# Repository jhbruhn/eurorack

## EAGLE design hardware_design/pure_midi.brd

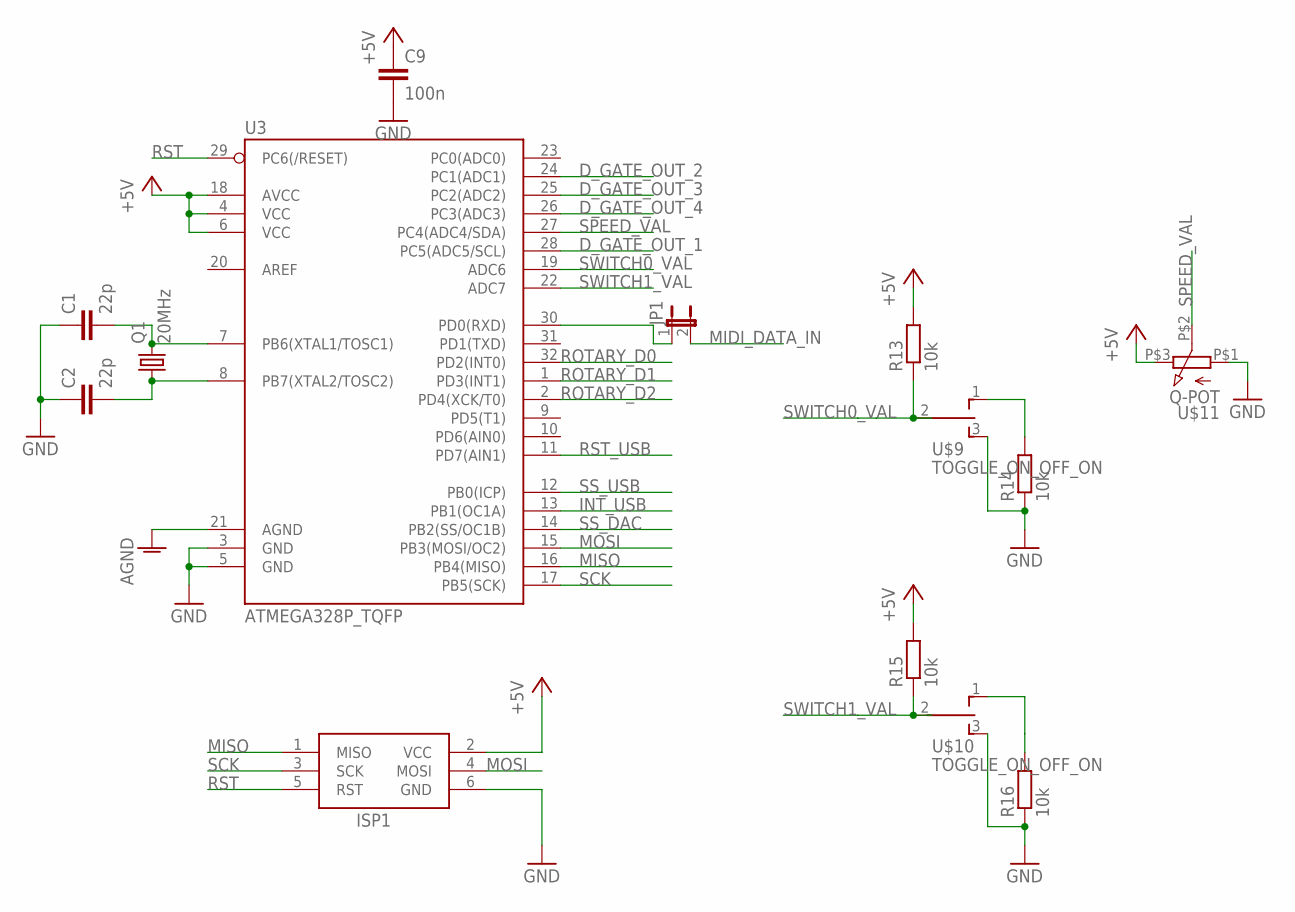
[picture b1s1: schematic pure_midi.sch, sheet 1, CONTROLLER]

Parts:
C1, C2: 22p; C0805
C9: 100n; C0805
ISP1: AVRISP-6; AVRISP
JP1: JP1E; JP1
Q1: 20MHz; HC49UP
R13, R14, R15, R16: 10k; R0805
U3: ATMEGA328P_TQFP; TQFP32-08
U$9, U$10: TOGGLE_ON_OFF_ON
U$11: Q-POT

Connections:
+5V: C9.1, ISP1.2 (VCC), R13.2, R15.2, U3.4 (VCC), U3.6 (VCC), U3.18 (AVCC), U$11.P$3 (3); also elsewhere on the board
D_GATE_OUT_1: U3.28 (PC5(ADC5/SCL)); also elsewhere on the board
D_GATE_OUT_2: U3.24 (PC1(ADC1)); also elsewhere on the board
D_GATE_OUT_3: U3.25 (PC2(ADC2)); also elsewhere on the board
D_GATE_OUT_4: U3.26 (PC3(ADC3)); also elsewhere on the board
GND: C1.1, C2.1, C9.2, ISP1.6 (GND), R14.1, R16.1, U3.3 (GND), U3.5 (GND), U3.21 (AGND), U$9.3 (S), U$10.3 (S), U$11.P$1 (1); also elsewhere on the board
INT_USB: U3.13 (PB1(OC1A)); also elsewhere on the board
MIDI_DATA_IN: JP1.2; also elsewhere on the board
MISO: ISP1.1 (MISO), U3.16 (PB4(MISO)); also elsewhere on the board
MOSI: ISP1.4 (MOSI), U3.15 (PB3(MOSI/OC2)); also elsewhere on the board
unnamed: C1.2, Q1.2, U3.7 (PB6(XTAL1/TOSC1))
unnamed: C2.2, Q1.1, U3.8 (PB7(XTAL2/TOSC2))
unnamed: JP1.1, U3.30 (PD0(RXD))
unnamed: R16.2, U$10.1 (O)
unnamed: R14.2, U$9.1 (O)
ROTARY_D0: U3.32 (PD2(INT0)); also elsewhere on the board
ROTARY_D1: U3.1 (PD3(INT1)); also elsewhere on the board
ROTARY_D2: U3.2 (PD4(XCK/T0)); also elsewhere on the board
RST: ISP1.5 (RST), U3.29 (PC6(/RESET))
RST_USB: U3.11 (PD7(AIN1)); also elsewhere on the board
SCK: ISP1.3 (SCK), U3.17 (PB5(SCK)); also elsewhere on the board
SPEED_VAL: U3.27 (PC4(ADC4/SDA)), U$11.P$2 (2)
SS_DAC: U3.14 (PB2(SS/OC1B)); also elsewhere on the board
SS_USB: U3.12 (PB0(ICP)); also elsewhere on the board
SWITCH0_VAL: R13.1, U3.19 (ADC6), U$9.2
SWITCH1_VAL: R15.1, U3.22 (ADC7), U$10.2

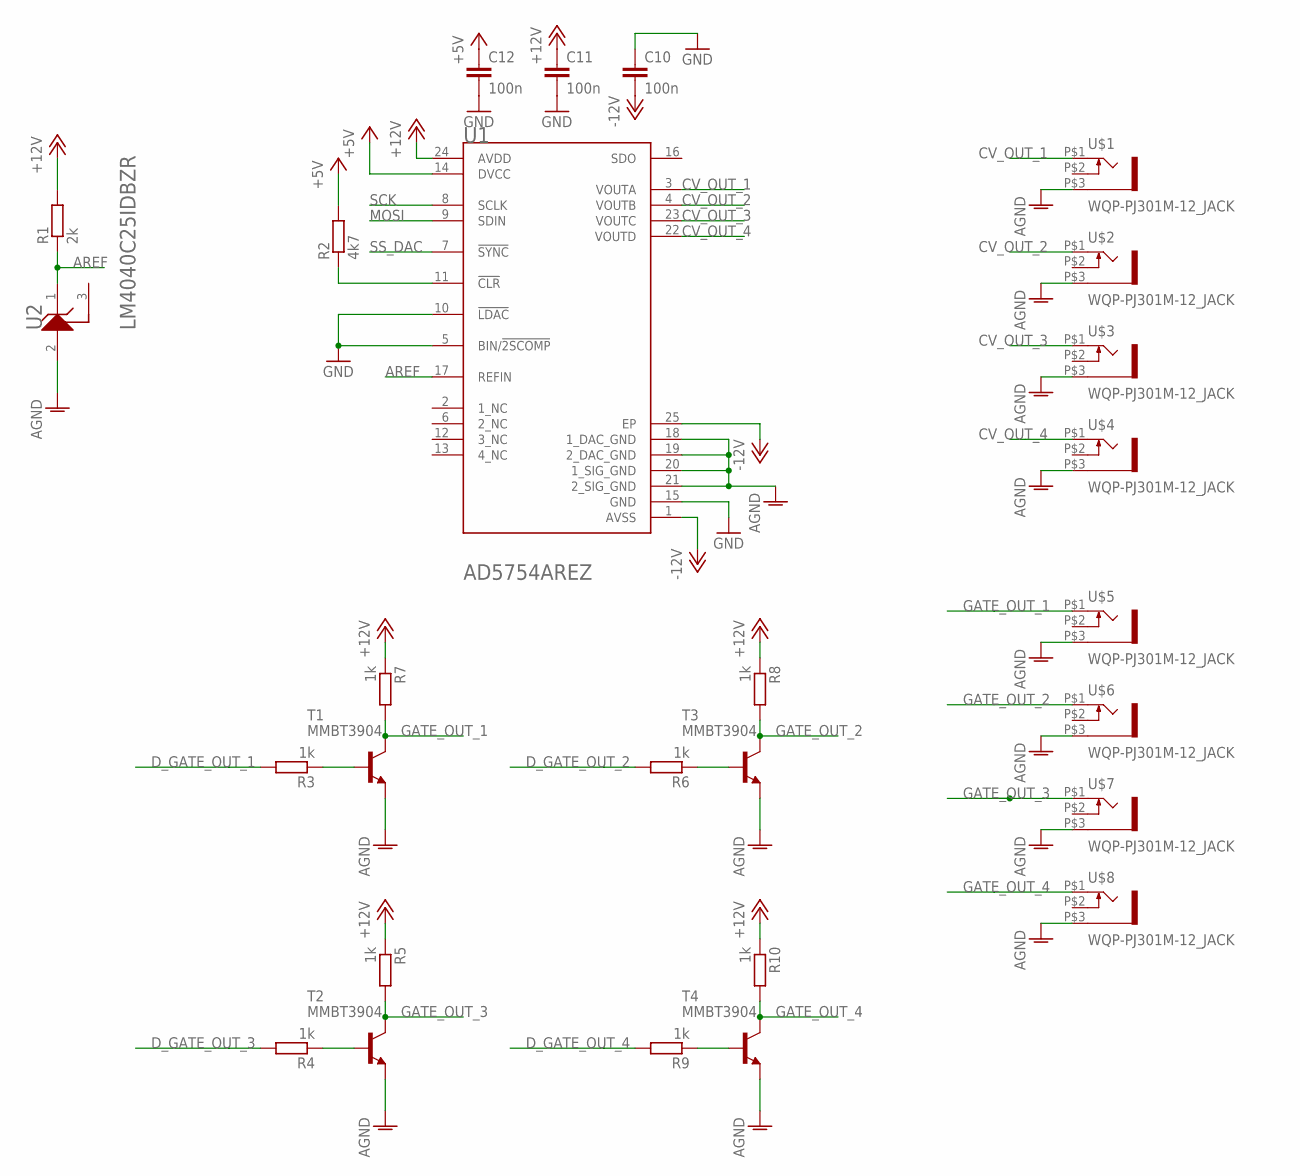
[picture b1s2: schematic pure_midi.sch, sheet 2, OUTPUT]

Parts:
C10, C11, C12: 100n; C0805
R1: 2k; R0805
R2: 4k7; R0805
R3, R4, R5, R6, R7, R8, R9, R10: 1k; R0805
T1, T2, T3, T4: MMBT3904; SOT23-EBC
U1: ANALOG_DEVICES_INC_AD5754AREZANALOG_DEVICES_INC_A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; ANALOG_DEVICES_INC_AD5754AREZ_0
U2: TEXAS_INSTRUMENTS_LM4040C25IDBZRTEXAS_INSTRUMENTS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; TEXAS_INSTRUMENTS_LM4040C25IDBZR_1
U$1, U$2, U$3, U$4, U$5, U$6, U$7, U$8: WQP-PJ301M-12_JACK

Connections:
+5V: C12.1, R2.2, U1.14 (DVCC); also elsewhere on the board
+12V: C11.1, R1.2, R5.1, R7.1, R8.1, R10.1, U1.24 (AVDD); also elsewhere on the board
-12V: C10.2, U1.1 (AVSS), U1.25 (EP); also elsewhere on the board
AREF: R1.1, U1.17 (REFIN), U2.1 (CATHODE)
CV_OUT_1: U1.3 (VOUTA), U$1.P$1 (2)
CV_OUT_2: U1.4 (VOUTB), U$2.P$1 (2)
CV_OUT_3: U1.23 (VOUTC), U$3.P$1 (2)
CV_OUT_4: U1.22 (VOUTD), U$4.P$1 (2)
D_GATE_OUT_1: R3.2; also elsewhere on the board
D_GATE_OUT_2: R6.2; also elsewhere on the board
D_GATE_OUT_3: R4.2; also elsewhere on the board
D_GATE_OUT_4: R9.2; also elsewhere on the board
GATE_OUT_1: R7.2, T1.C, U$5.P$1 (2)
GATE_OUT_2: R8.2, T3.C, U$6.P$1 (2)
GATE_OUT_3: R5.2, T2.C, U$7.P$1 (2)
GATE_OUT_4: R10.2, T4.C, U$8.P$1 (2)
GND: C10.1, C11.2, C12.2, T1.E, T2.E, T3.E, T4.E, U1.5 (BIN/!2SCOMP!), U1.10 (!LDAC!), U1.15 (GND), U1.18 (1_DAC_GND), U1.19 (2_DAC_GND), U1.20 (1_SIG_GND), U1.21 (2_SIG_GND), U2.2 (ANODE), U$1.P$3 (1), U$2.P$3 (1), U$3.P$3 (1), U$4.P$3 (1), U$5.P$3 (1), U$6.P$3 (1), U$7.P$3 (1), U$8.P$3 (1); also elsewhere on the board
MOSI: U1.9 (SDIN); also elsewhere on the board
unnamed: R2.1, U1.11 (!CLR!)
unnamed: R3.1, T1.B
unnamed: R4.1, T2.B
unnamed: R6.1, T3.B
unnamed: R9.1, T4.B
SCK: U1.8 (SCLK); also elsewhere on the board
SS_DAC: U1.7 (!SYNC!); also elsewhere on the board

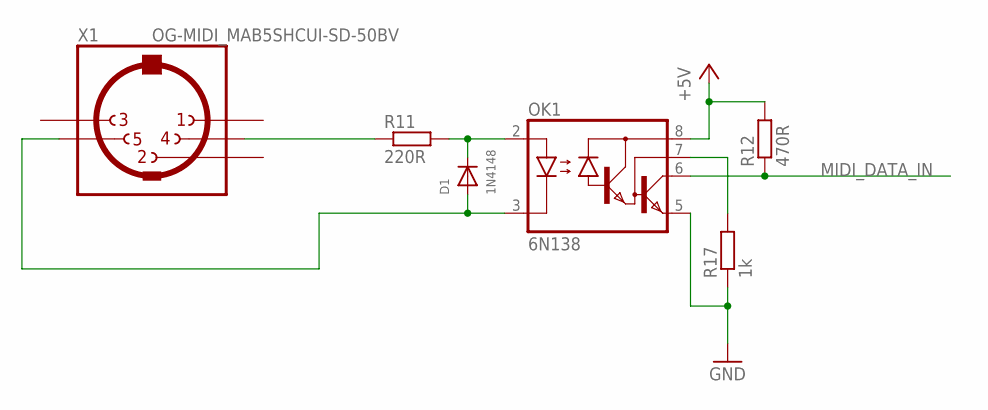
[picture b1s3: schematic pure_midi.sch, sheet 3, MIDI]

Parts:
D1: 1N4148; SOD-323F
OK1: 6N138; DIL08
R11: 220R; R0805
R12: 470R; R0805
R17: 1k; R0805
X1: OG-MIDI_MAB5SHCUI-SD-50BV; OG-MIDI_SD-50BV

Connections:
+5V: OK1.8 (VCC), R12.2; also elsewhere on the board
GND: OK1.5 (GND), R17.1; also elsewhere on the board
MIDI_DATA_IN: OK1.6 (VO), R12.1; also elsewhere on the board
unnamed: D1.C, OK1.2 (A), R11.2
unnamed: R11.1, X1.4
unnamed: D1.A, OK1.3 (C), X1.5
unnamed: OK1.7 (VB), R17.2

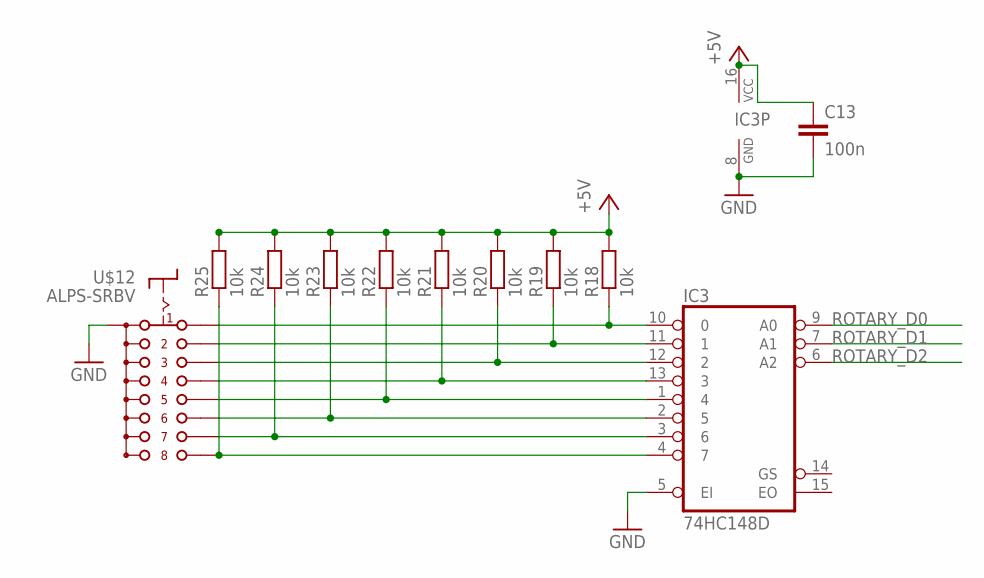
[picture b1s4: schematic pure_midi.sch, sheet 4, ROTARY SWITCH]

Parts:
C13: 100n; C0805
IC3: 74HC148D; SO16
R18, R19, R20, R21, R22, R23, R24, R25: 10k; R0805
U$12: ALPS-SRBV

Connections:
+5V: C13.1, IC3.16 (VCC), R18.2, R19.2, R20.2, R21.2, R22.2, R23.2, R24.2, R25.2; also elsewhere on the board
GND: C13.2, IC3.5 (EI), IC3.8 (GND), U$12.COM (A), U$12.COM2 (A); also elsewhere on the board
unnamed: IC3.10 (0), R18.1, U$12.A (1)
unnamed: IC3.11 (1), R19.1, U$12.B (2)
unnamed: IC3.12 (2), R20.1, U$12.C (3)
unnamed: IC3.13 (3), R21.1, U$12.D (4)
unnamed: IC3.1 (4), R22.1, U$12.E (5)
unnamed: IC3.2 (5), R23.1, U$12.F (6)
unnamed: IC3.3 (6), R24.1, U$12.G (7)
unnamed: IC3.4 (7), R25.1, U$12.H (8)
ROTARY_D0: IC3.9 (A0); also elsewhere on the board
ROTARY_D1: IC3.7 (A1); also elsewhere on the board
ROTARY_D2: IC3.6 (A2); also elsewhere on the board

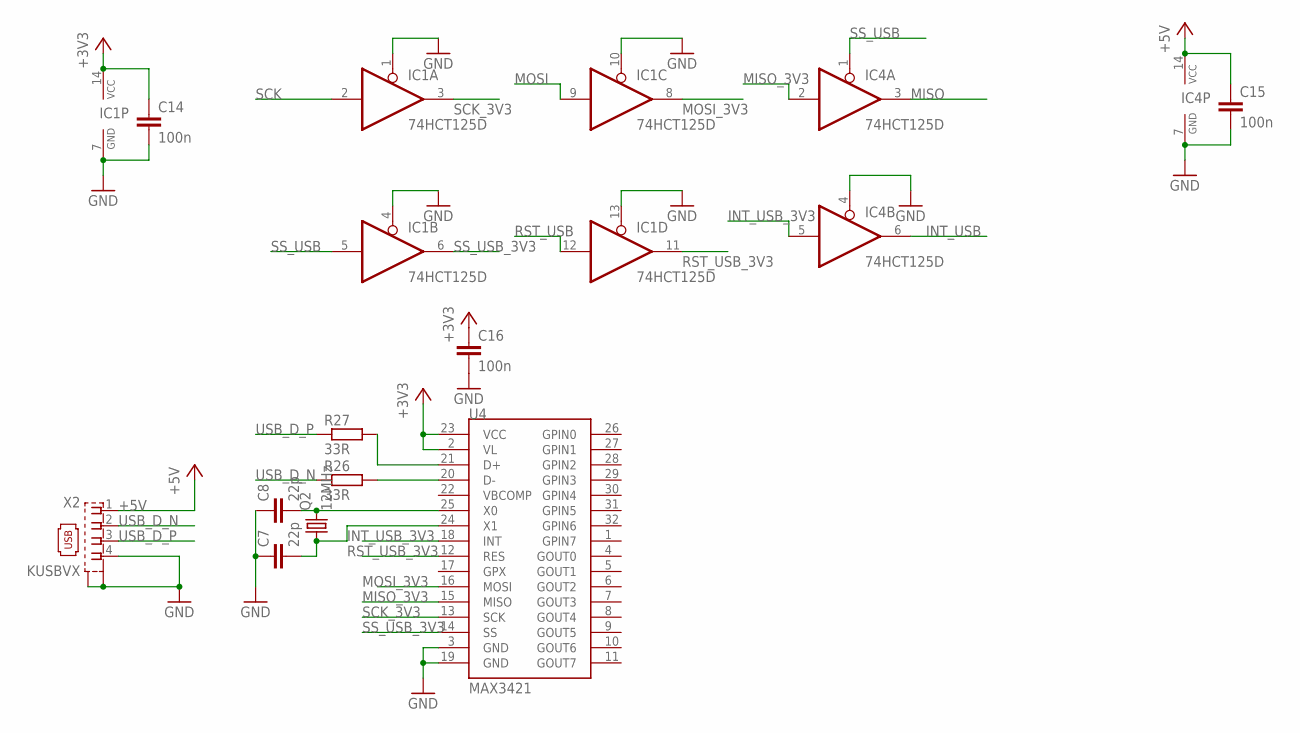
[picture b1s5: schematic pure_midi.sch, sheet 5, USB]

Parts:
C7, C8: 22p; C0805
C14, C15, C16: 100n; C0805
IC1, IC4: 74HCT125D; SO14
Q2: 12MHz; HC49UP
R26, R27: 33R; R0805
U4: MAX3421; TQFP32-5MM
X2: KUSBVX

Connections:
+3V3: C14.1, C16.1, IC1.14 (VCC), U4.2 (VL), U4.23 (VCC); also elsewhere on the board
+5V: C15.1, IC4.14 (VCC), X2.1; also elsewhere on the board
GND: C7.1, C8.1, C14.2, C15.2, C16.2, IC1.1 (OE), IC1.4 (OE), IC1.7 (GND), IC1.10 (OE), IC1.13 (OE), IC4.4 (OE), IC4.7 (GND), U4.3 (GND), U4.19 (GND), X2.4, X2.M1 (S1), X2.M2 (S2); also elsewhere on the board
INT_USB: IC4.6 (O); also elsewhere on the board
INT_USB_3V3: IC4.5 (I), U4.18 (INT)
MISO: IC4.3 (O); also elsewhere on the board
MISO_3V3: IC4.2 (I), U4.15 (MISO)
MOSI: IC1.9 (I); also elsewhere on the board
MOSI_3V3: IC1.8 (O), U4.16 (MOSI)
unnamed: C8.2, Q2.2, U4.25 (X0)
unnamed: C7.2, Q2.1, U4.24 (X1)
RST_USB: IC1.12 (I); also elsewhere on the board
RST_USB_3V3: IC1.11 (O), U4.12 (RES)
SCK: IC1.2 (I); also elsewhere on the board
SCK_3V3: IC1.3 (O), U4.13 (SCK)
SS_USB: IC1.5 (I), IC4.1 (OE); also elsewhere on the board
SS_USB_3V3: IC1.6 (O), U4.14 (SS)
USB_D_N: R26.1, X2.2
USB_D_P: R27.1, X2.3
USB_N: R26.2, U4.20 (D-)
USB_P: R27.2, U4.21 (D+)

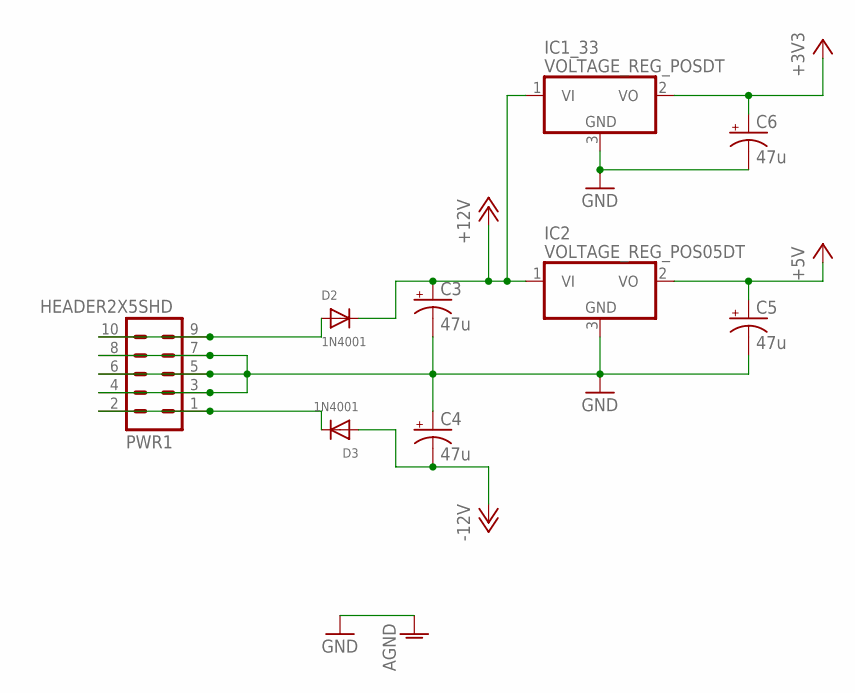
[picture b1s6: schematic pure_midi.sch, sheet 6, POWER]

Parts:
C3, C4, C5, C6: 47u; 153CLV-0505
D2, D3: 1N4001; SMADIODE
IC1_33: VOLTAGE_REG_POSDT; TO252
IC2: VOLTAGE_REG_POS05DT; TO252
PWR1: HEADER2X5SHD; 2X5-SHROUDED

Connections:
+3V3: C6.+, IC1_33.2 (VO); also elsewhere on the board
+5V: C5.+, IC2.2 (VO); also elsewhere on the board
+12V: C3.+, D2.C, IC1_33.1 (VI), IC2.1 (VI); also elsewhere on the board
-12V: C4.-, D3.A; also elsewhere on the board
GND: C3.-, C4.+, C5.-, C6.-, IC1_33.3 (GND), IC2.3 (GND), PWR1.3, PWR1.4, PWR1.5, PWR1.6, PWR1.7, PWR1.8; also elsewhere on the board
unnamed: D2.A, PWR1.9, PWR1.10
unnamed: D3.C, PWR1.1, PWR1.2

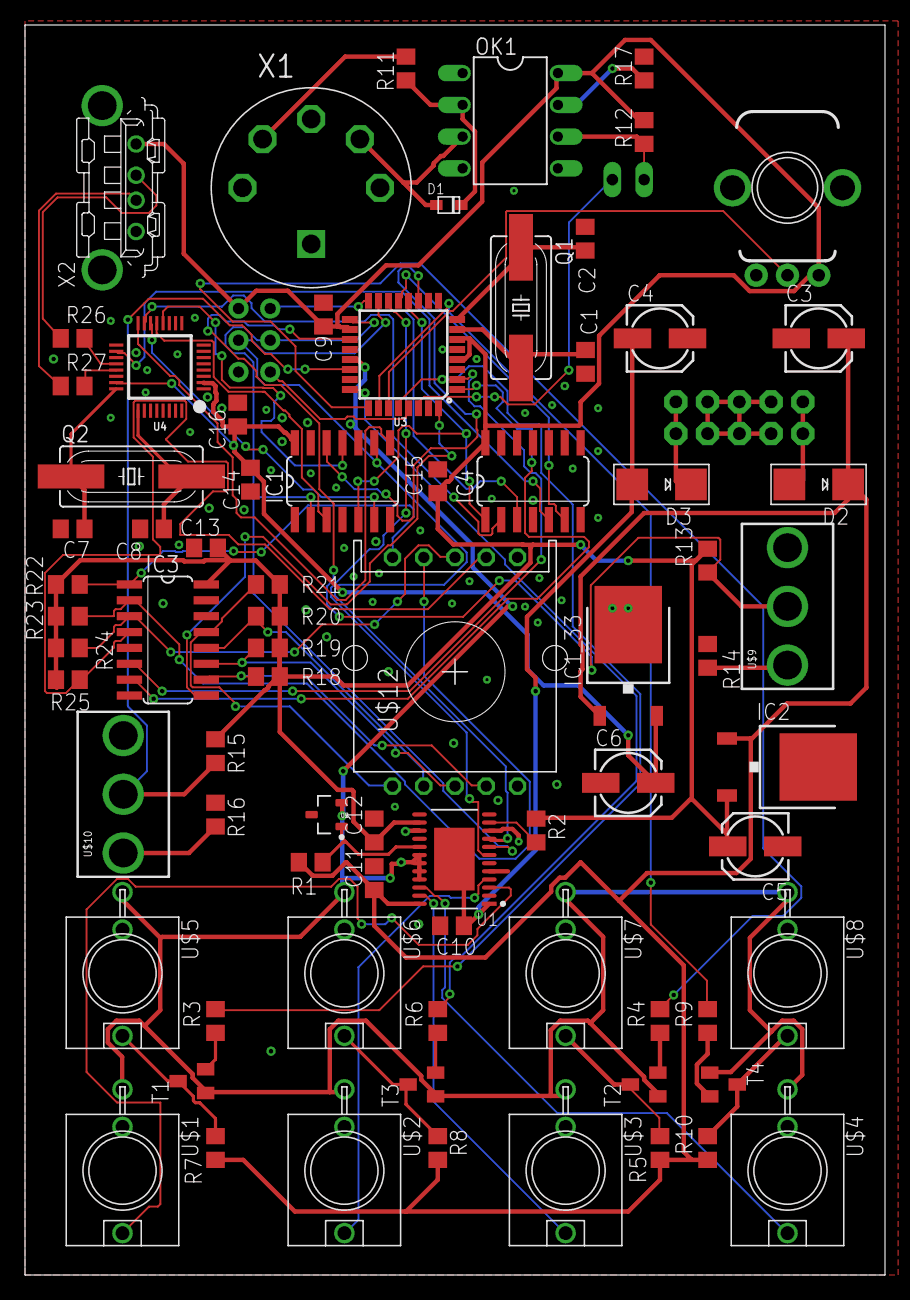
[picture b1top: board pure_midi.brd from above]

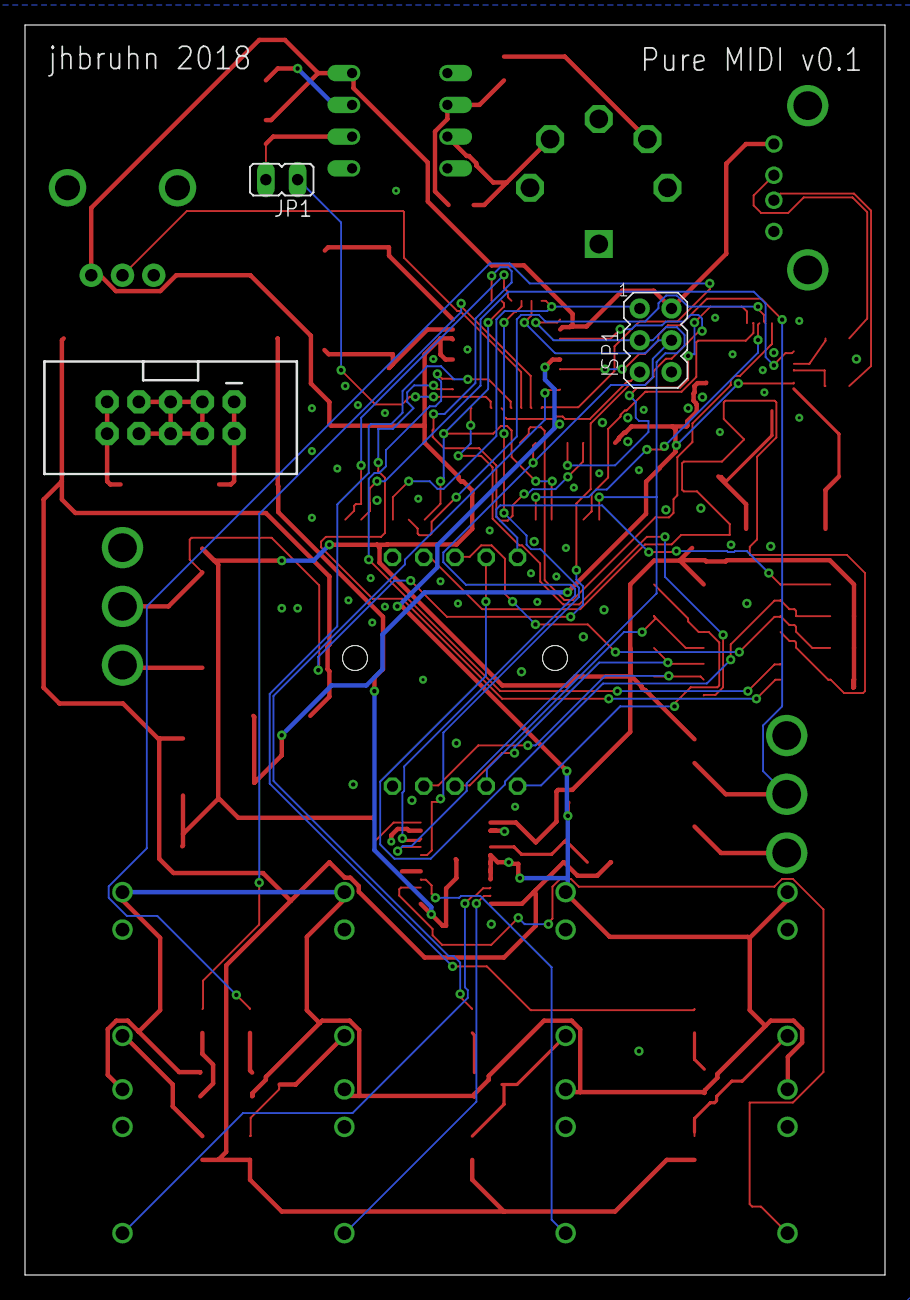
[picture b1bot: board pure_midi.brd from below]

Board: 2 copper layers, 68.8 x 100.0 mm, 79 parts (3 on the bottom side), 69 nets.

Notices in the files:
parts and their libraries:
SparkFun-IC-Microcontroller: Licensing: Creative Commons ShareAlike 4.0 International - https://creativecommons.org/licenses/by-sa/4.0
op-amp: Copyright (C) 2006 by Bob Starr
